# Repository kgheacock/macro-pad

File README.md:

# macro-pad

Firmware for a custom 6-key emoji macro keyboard.

See [`tasks/`](tasks/) for the task backlog.

## Layout

```
firmware/  CircuitPython firmware — contents copy to CIRCUITPY
driver/    Host-side driver / controller code
inbox/     Per-channel message inbox: SQLite store and `inbox` CLI (Node)
hardware/  PCB, wiring, and enclosure design files
test/      Test suites
docs/      Requirements and hardware notes
tasks/     Task specs (see tasks/README.md)
```

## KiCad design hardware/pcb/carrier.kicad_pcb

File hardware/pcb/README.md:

# Carrier board

A 90 × 70 mm, 2-layer board that replaces the perfboard. The Pimoroni Pico Plus 2 plugs into two
female headers, each ScreenKey plugs into its own 1.25 mm 9-pin socket, and the I2S mic gets a
6-pin header. All the shared lines (3V3, GND, CLK, DC, RST, BL) are copper, and GND is poured on both layers.

**To order:** upload `carrier_jlcpcb.zip` to JLCPCB. The defaults are fine: 2 layers, 1.6 mm, 1 oz, HASL.
`carrier_top.png` and `carrier_bottom.png` show the copper.

## Assembly by JLCPCB

To have JLCPCB solder the parts on, upload `carrier_bom.csv` and `carrier_cpl.csv` at the PCBA step:
- Choose **Parts Selection: By JLCPCB (Manual Match)**, since the BOM gives descriptions and an MPN but no LCSC numbers.
- Set **Confirm Parts Placement: Yes** so they check the through-hole positions and rotations.
- The mic header (J3) is left off. Solder it yourself once you've checked your mic's pin order.

## Parts

| Ref | Part | Qty |
|---|---|---|
| J1, J2 | 1×20 female header, 2.54 mm (low-profile saves about 3 mm) | 2 |
| K0–K5 | 1.25 mm 9-pin vertical through-hole socket: Molex PicoBlade 53047-0910, or a generic "MX1.25 9P vertical" | 6 |
| J3 | 1×6 male header, 2.54 mm | 1 |
| C1 | 10 µF 16 V electrolytic, radial, 5 mm body, 2 mm lead pitch. + goes to the square pad | 1 |
| — | 1.25 mm 9-pin cable with a connector at both ends, 10 cm, wired pin 1 to pin 1 | 6 |
| — | M3 screws for the 4 mounting holes (3.2 mm, 4 mm in from each corner) | 4 |

## Pinout

- **Key sockets.** Pins 1 to 9 are RST, BL, 3V3, GND, DIN, CLK, CS, DC, KEY. These match the module's
  own connector (H2 in `docs/0.85inch_ScreenKey_Module.pdf`), so each cable must carry pin 1 to pin 1.
  Check one with a multimeter before plugging in a key. Socket K*n* is key *n* in `firmware/pins.py`.
- **Pico.** It plugs in with its USB-C end toward the `<USB-C` mark. J1 is Pico pins 1 to 20, and J2 is
  pins 40 to 21.
- **Mic.** J3 is SEL, LRCL, DOUT, BCLK, GND, 3V, in the order of Adafruit's SPH0645 breakout.
  SEL is tied to GND (left channel). Check your breakout's order before soldering it on.

## Rebuild

`make -C hardware/pcb FREEROUTING=/path/to/freerouting-1.9.0.jar` needs KiCad 7, Java and `xvfb-run`.
`build_carrier.py` holds the placement and nets. Freerouting does the routing, and the run ends
with a DRC report in `drc.rpt`. The committed board has 0 unconnected pads and no clearance errors.
Its only warnings are footprint-library notices and 7 GND pads with thermal spokes on one layer only.

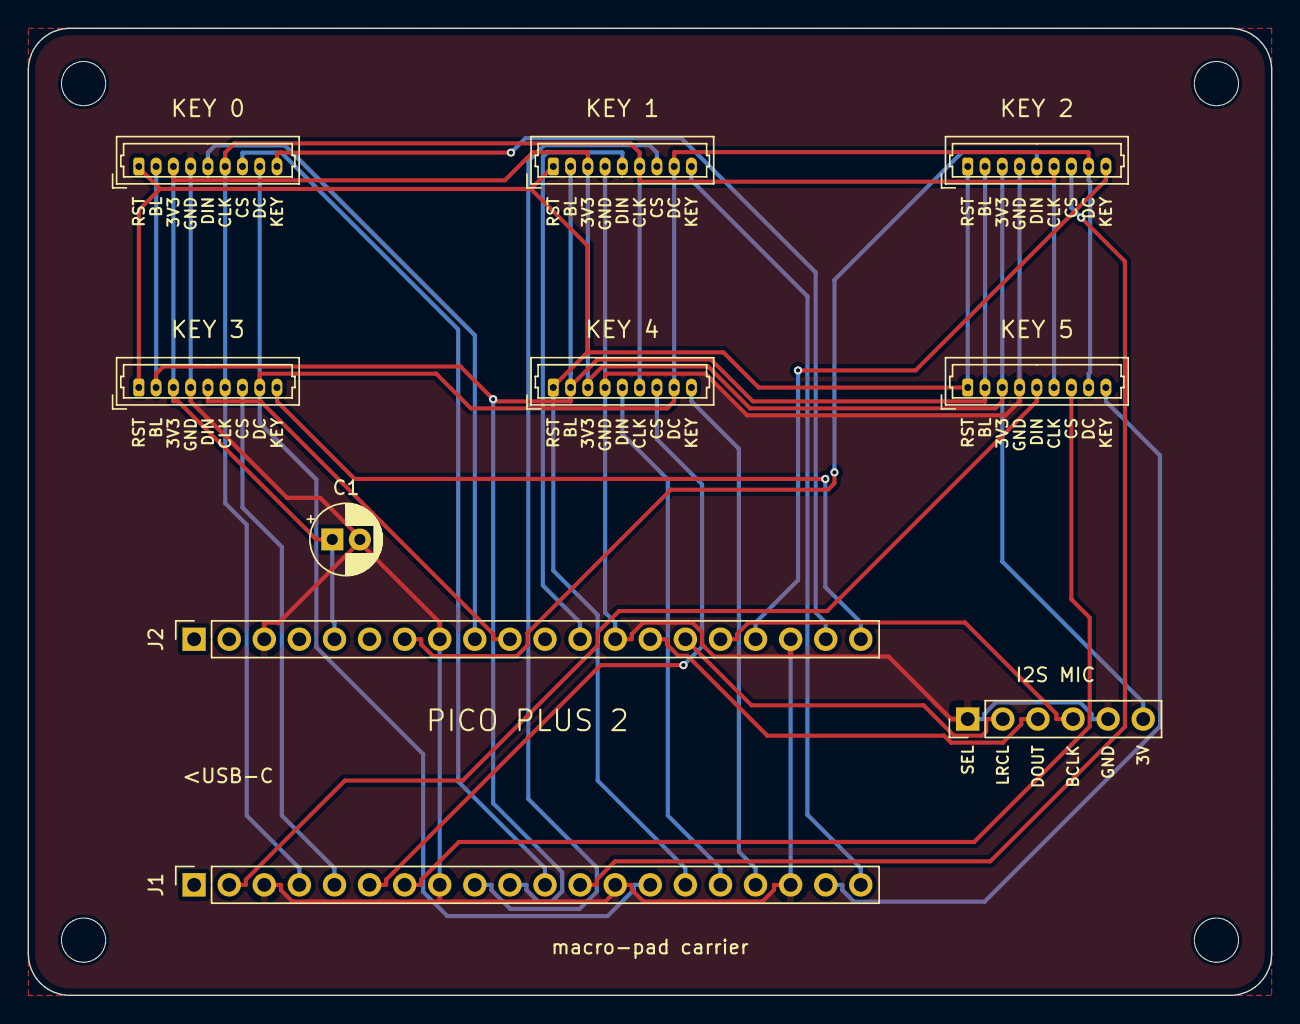
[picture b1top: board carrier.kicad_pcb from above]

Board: 2 copper layers, 90.0 x 70.0 mm, 14 parts (0 on the bottom side), 27 nets.

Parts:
C1: 10uF 16V; CP_Radial_D5.0mm_P2.00mm
H1, H2, H3, H4: MountingHole_3.2mm_M3
J1: Pico pins 1-20; PinSocket_1x20_P2.54mm_Vertical
J2: Pico pins 40-21; PinSocket_1x20_P2.54mm_Vertical
J3: I2S mic; PinHeader_1x06_P2.54mm_Vertical
K0: ScreenKey 0; Molex_PicoBlade_53047-0910_1x09_P1.25mm_Vertical
K1: ScreenKey 1; Molex_PicoBlade_53047-0910_1x09_P1.25mm_Vertical
K2: ScreenKey 2; Molex_PicoBlade_53047-0910_1x09_P1.25mm_Vertical
K3: ScreenKey 3; Molex_PicoBlade_53047-0910_1x09_P1.25mm_Vertical
K4: ScreenKey 4; Molex_PicoBlade_53047-0910_1x09_P1.25mm_Vertical
K5: ScreenKey 5; Molex_PicoBlade_53047-0910_1x09_P1.25mm_Vertical

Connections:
3V3: C1.1, J2.5, J3.6, K0.3, K1.3, K2.3, K3.3, K4.3, K5.3
BL: J1.10, K0.2, K1.2, K2.2, K3.2, K4.2, K5.2
CLK: J1.4, K0.6, K1.6, K2.6, K3.6, K4.6, K5.6
DC: J1.14, K0.8, K1.8, K2.8, K3.8, K4.8, K5.8
GND: C1.2, J1.3, J1.8, J1.13, J1.18, J2.3, J2.8, J2.13, J2.18, J3.1, J3.5, K0.4, K1.4, K2.4, K3.4, K4.4, K5.4
K0_CS: J1.11, K0.7
K0_DIN: J2.9, K0.5
K0_KEY: J2.19, K0.9
K1_CS: J1.9, K1.7
K1_DIN: J2.12, K1.5
K1_KEY: J1.20, K1.9
K2_CS: J1.12, K2.7
K2_DIN: J2.7, K2.5
K2_KEY: J2.17, K2.9
K3_CS: J1.5, K3.7
K3_DIN: J2.10, K3.5
K3_KEY: J2.20, K3.9
K4_CS: J1.6, K4.7
K4_DIN: J1.16, K4.5
K4_KEY: J1.17, K4.9
K5_CS: J1.7, K5.7
K5_DIN: J1.2, K5.5
K5_KEY: J1.19, K5.9
MIC_BCLK: J2.16, J3.4
MIC_DATA: J2.14, J3.3
MIC_WS: J2.15, J3.2
RST: J1.15, K0.1, K1.1, K2.1, K3.1, K4.1, K5.1
